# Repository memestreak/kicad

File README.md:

# KiCad

This repo contains my Kicad projects, custom libraries, and settings.

## Libraries

*   Footprints: `jme.pretty/`.
*   Symbols: `jme-symbols.kicad_sym`.

## Projects

Various projects, mostly related to audio and Eurorack.
                 
## Preferences

In the version-specific directories there are KiCad user preferences.

In order for KiCad to use them, you should replace the existing KiCad
user preference directory with a soft link to this directory.

E.g.,

```
# On Mac, for Kicad 7.0:

mv ~/Library/Preferences/kicad/7.0 ~/~/Library/Preferences/kicad/7.0_orig
ln -s ~/repos/kicad/7.0/preferences ~/Library/Preferences/kicad/7.0
```

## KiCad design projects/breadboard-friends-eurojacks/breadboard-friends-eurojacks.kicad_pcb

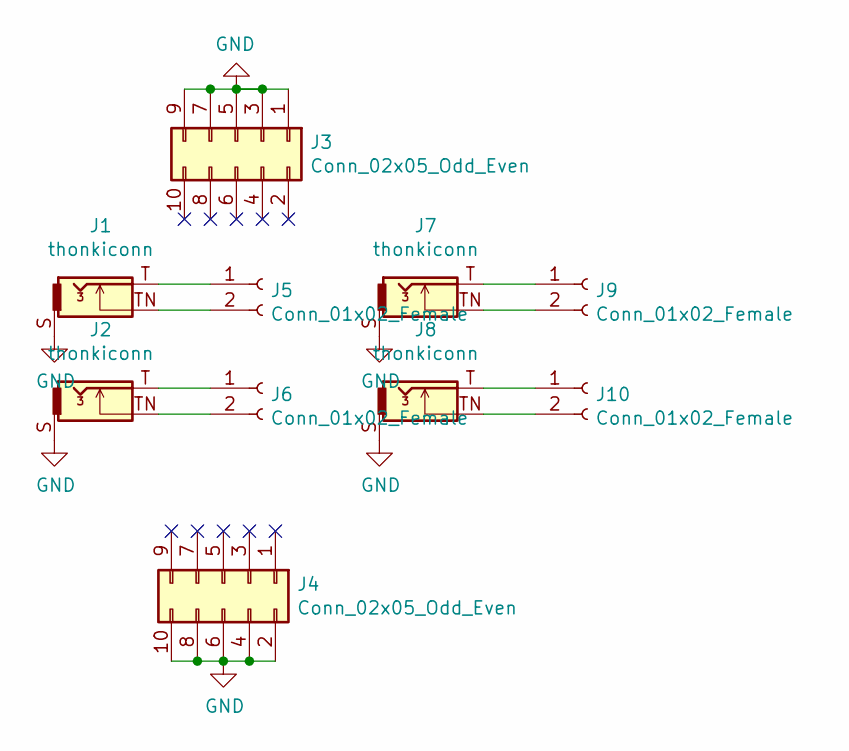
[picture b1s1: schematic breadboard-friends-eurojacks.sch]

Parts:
J1, J2, J7, J8: thonkiconn; Jack_3.5mm_QingPu_WQP-PJ398SM_Vertical_CircularHoles
J3, J4: Conn_02x05_Odd_Even; PinHeader_2x05_P2.54mm_Vertical
J5, J6, J9, J10: Conn_01x02_Female; PinSocket_1x02_P2.54mm_Vertical

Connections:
GND: J1.S, J2.S, J3.1, J3.3, J3.5, J3.7, J3.9, J4.2, J4.4, J4.6, J4.8, J4.10, J7.S, J8.S
unnamed: J1.T, J5.1
unnamed: J1.TN, J5.2
unnamed: J2.T, J6.1
unnamed: J2.TN, J6.2
unnamed: J7.T, J9.1
unnamed: J7.TN, J9.2
unnamed: J8.T, J10.1
unnamed: J8.TN, J10.2

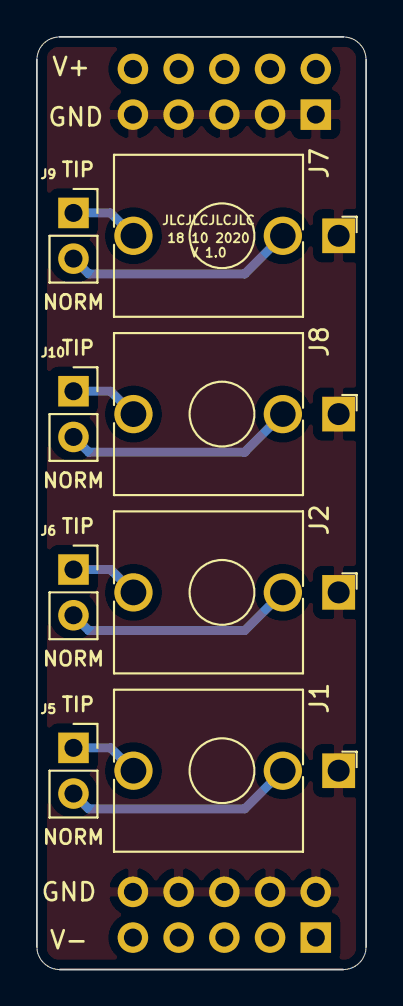
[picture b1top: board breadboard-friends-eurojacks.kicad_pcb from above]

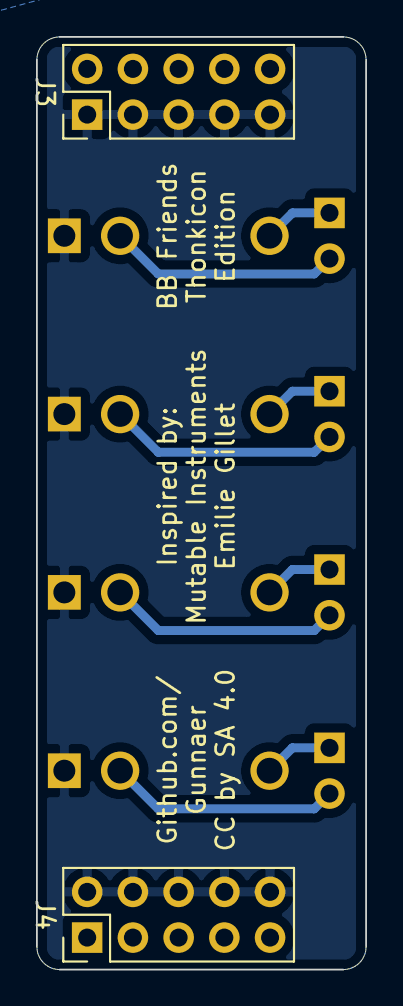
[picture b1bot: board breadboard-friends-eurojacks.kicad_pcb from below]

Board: 2 copper layers, 18.3 x 51.8 mm, 10 parts (2 on the bottom side), 9 nets.

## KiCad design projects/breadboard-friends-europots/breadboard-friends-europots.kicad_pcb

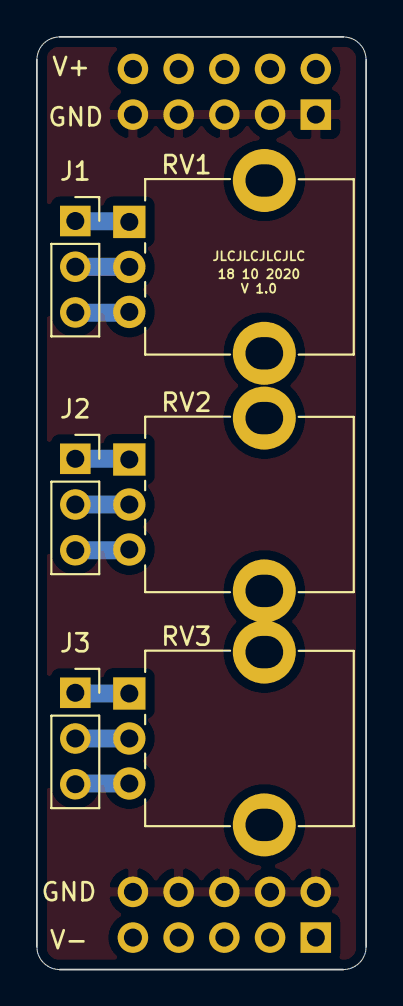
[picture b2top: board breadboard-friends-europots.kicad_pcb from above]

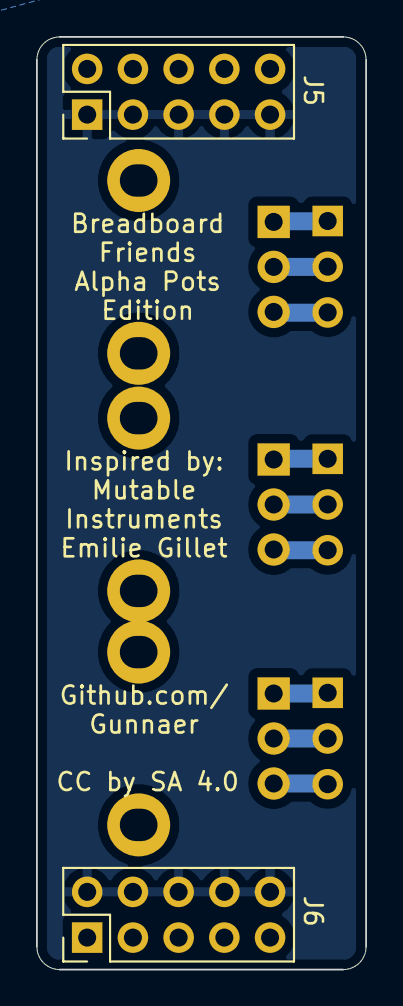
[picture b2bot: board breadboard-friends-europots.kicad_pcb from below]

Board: 2 copper layers, 18.3 x 51.8 mm, 8 parts (2 on the bottom side), 10 nets.

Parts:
J1, J2, J3: Conn_01x03_Female; PinSocket_1x03_P2.54mm_Vertical
J5, J6: Conn_02x05_Odd_Even; PinHeader_2x05_P2.54mm_Vertical
RV1, RV2, RV3: R_POT; Alpha_Potentiometer_2.1mmOval_Holes

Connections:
GND: J5.1, J5.3, J5.5, J5.7, J5.9, J6.2, J6.4, J6.6, J6.8, J6.10
unnamed: J1.1, RV1.1
unnamed: J1.2, RV1.2
unnamed: J1.3, RV1.3
unnamed: J2.1, RV2.1
unnamed: J2.2, RV2.2
unnamed: J2.3, RV2.3
unnamed: J3.1, RV3.1
unnamed: J3.2, RV3.2
unnamed: J3.3, RV3.3

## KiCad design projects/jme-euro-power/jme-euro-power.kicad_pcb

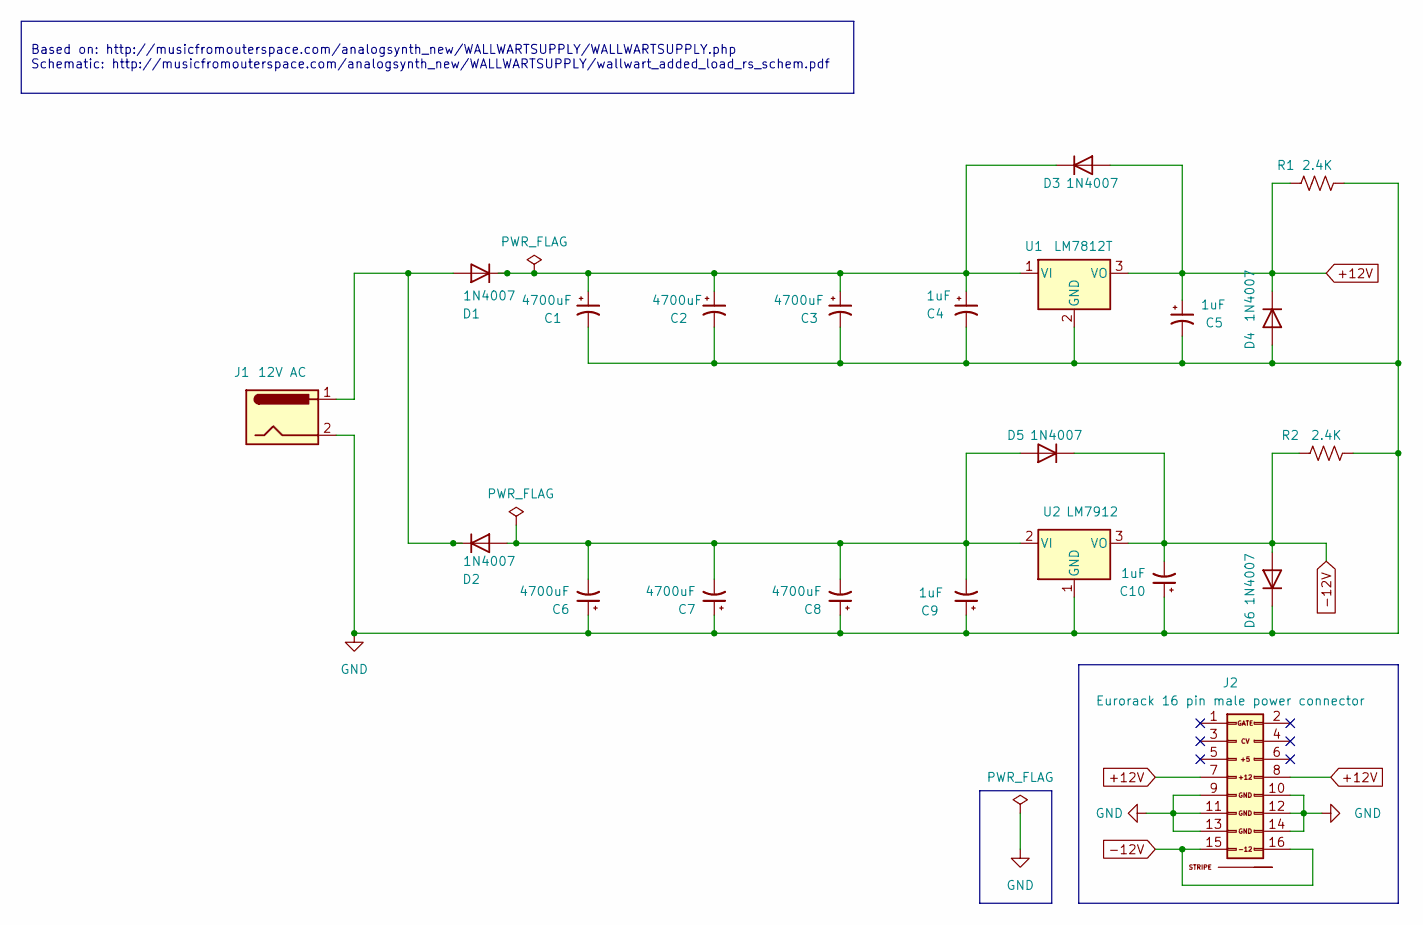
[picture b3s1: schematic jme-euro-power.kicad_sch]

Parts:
C1, C2, C3, C6, C7, C8: 4700uF; CP_Radial_D16.0mm_P7.50mm
C4, C5, C9, C10: 1uF; C_Disc_D7.5mm_W5.0mm_P5.00mm
D1: 1N4007; D_DO-35_P7.62mm_Horizontal
D2, D3, D4, D5, D6: 1N4007; D_DO-41_SOD81_P10.16mm_Horizontal
J1: 12V AC; BarrelJack_CUI_PJ-102AH_Horizontal
J2: Eurorack 16 pin male power connector; Pins_2x08_2.54mm_TH_EuroPower_Shrouded; Part Number LL1007-1 (2*8 HITEMP)
R1, R2: 2.4K; R_Box_L14.0mm_W5.0mm_P9.00mm
U1: LM7812T; TO-220-3_Vertical
U2: LM7912; TO-220-3_Vertical

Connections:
+12V: C5.1, D3.2 (A), D4.1 (K), J2.7 (12V), J2.8 (+12V), R1.1, U1.3 (VO)
-12V: C10.2, D5.1 (K), D6.2 (A), J2.15 (-12V), J2.16, R2.1, U2.3 (VO)
GND: C1.2, C2.2, C3.2, C4.2, C5.2, C6.1, C7.1, C8.1, C9.1, C10.1, D4.2 (A), D6.1 (K), J1.2, J2.9 (GND), J2.10 (GND), J2.11 (GND), J2.12 (GND), J2.13 (-12), J2.14 (-12V), R1.2, R2.2, U1.2 (GND), U2.1 (GND)
unnamed: D1.2 (A), D2.1 (K), J1.1
unnamed: C1.1, C2.1, C3.1, C4.1, D1.1 (K), D3.1 (K), U1.1 (VI)
unnamed: C6.2, C7.2, C8.2, C9.2, D2.2 (A), D5.2 (A), U2.2 (VI)

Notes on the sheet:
Based on: http://musicfromouterspace.com/analogsynth_new/WALLWARTSUPPLY/WALLWARTSUPPLY.php Schematic: http://musicfromouterspace.com/analogsynth_new/WALLWARTSUPPLY/wallwart_added_load_rs_schem.pdf

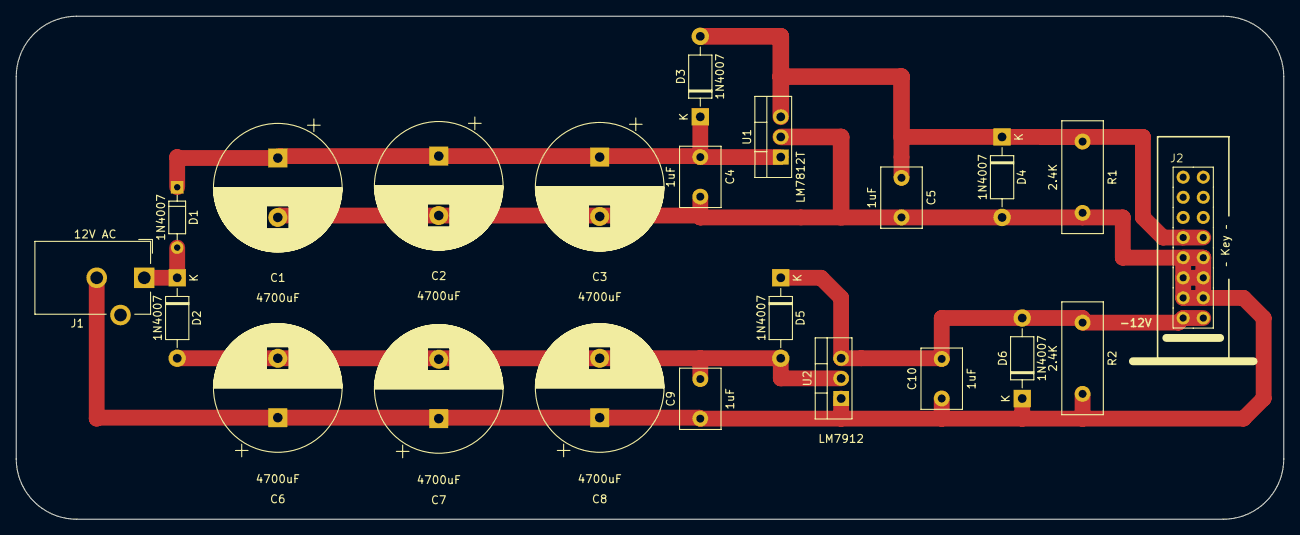
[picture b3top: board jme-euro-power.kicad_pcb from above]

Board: 2 copper layers, 160.0 x 63.5 mm, 22 parts (0 on the bottom side), 6 nets.

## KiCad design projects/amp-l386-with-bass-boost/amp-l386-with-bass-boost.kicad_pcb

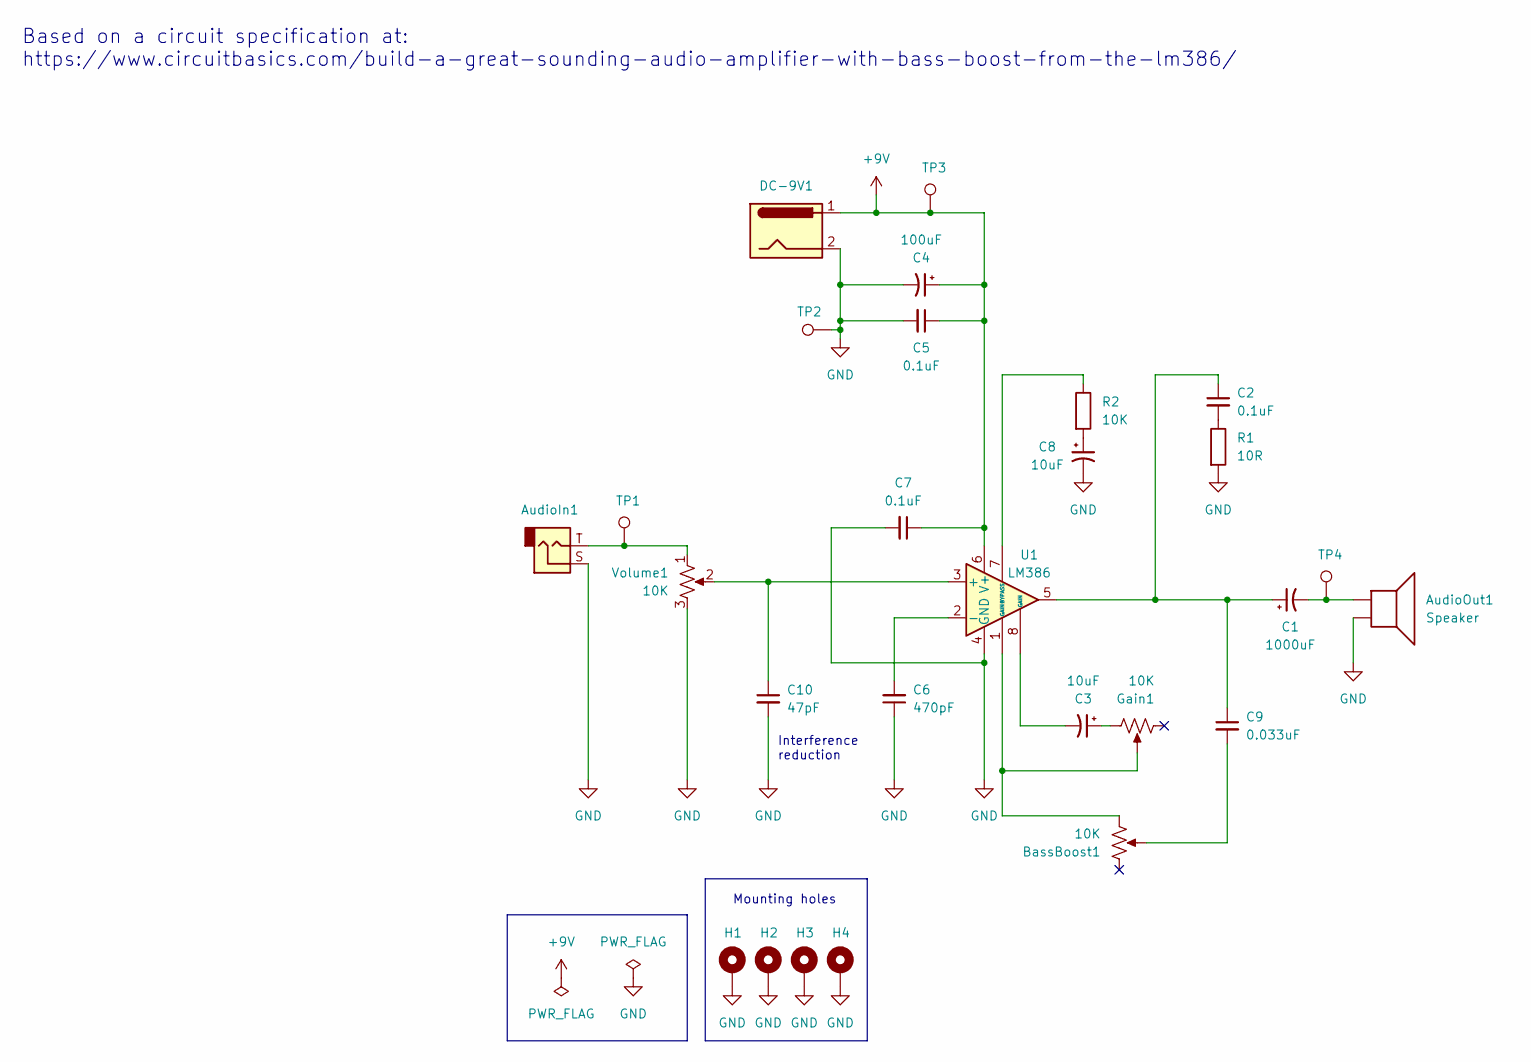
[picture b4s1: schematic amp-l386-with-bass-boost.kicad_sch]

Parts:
AudioIn1: AudioJack; jme-audio-pinheader-2.54-vertical
AudioOut1: Speaker; PinHeader_1x02_P2.54mm_Vertical
BassBoost1: 10K; PinHeader_1x03_P2.54mm_Vertical
C1: 1000uF; CP_Radial_D10.0mm_P5.00mm
C2, C7: 0.1uF; C_Disc_D5.1mm_W3.2mm_P5.00mm
C3, C8: 10uF; CP_Radial_D5.0mm_P2.50mm
C4: 100uF; CP_Radial_D6.3mm_P2.50mm
C5: 0.1uF; C_Rect_L7.0mm_W2.5mm_P5.00mm
C6: 470pF; C_Rect_L7.0mm_W2.5mm_P5.00mm
C9: 0.033uF; C_Disc_D5.1mm_W3.2mm_P5.00mm
C10: 47pF; C_Disc_D5.1mm_W3.2mm_P5.00mm
DC-9V1: Jack-DC; PinHeader_1x02_P2.54mm_Vertical
Gain1: 10K; PinHeader_1x03_P2.54mm_Vertical
H1, H2, H3, H4: MountingHole_Pad; MountingHole_3.2mm_M3_DIN965_Pad
R1: 10R; R_Axial_DIN0414_L11.9mm_D4.5mm_P20.32mm_Horizontal
R2: 10K; R_Axial_DIN0414_L11.9mm_D4.5mm_P20.32mm_Horizontal
TP1, TP2, TP3, TP4: TestPoint; TestPoint_Pad_2.0x2.0mm
U1: LM386; DIP-8_W7.62mm_Socket
Volume1: 10K; PinHeader_1x03_P2.54mm_Vertical

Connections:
+9V: C4.1, C5.1, C7.1, DC-9V1.1, TP3.1, U1.6 (V+)
GND: AudioIn1.S, AudioOut1.2, C4.2, C5.2, C6.1, C7.2, C8.2, C10.2, DC-9V1.2, H1.1, H2.1, H3.1, H4.1, R1.2, TP2.1, U1.4 (GND), Volume1.3
unnamed: AudioIn1.T, TP1.1, Volume1.1
unnamed: AudioOut1.1, C1.2, TP4.1
unnamed: BassBoost1.1, Gain1.2, U1.1 (GAIN)
unnamed: BassBoost1.2, C9.2
unnamed: C1.1, C2.1, C9.1, U1.5
unnamed: C2.2, R1.1
unnamed: C3.1, Gain1.3
unnamed: C3.2, U1.8 (GAIN)
unnamed: C6.2, U1.2 (-)
unnamed: C8.1, R2.2
unnamed: C10.1, U1.3 (+), Volume1.2
unnamed: R2.1, U1.7 (BYPASS)

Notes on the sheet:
Mounting holes
Based on a circuit specification at: https://www.circuitbasics.com/build-a-great-sounding-audio-amplifier-with-bass-boost-from-the-lm386/
Interference reduction

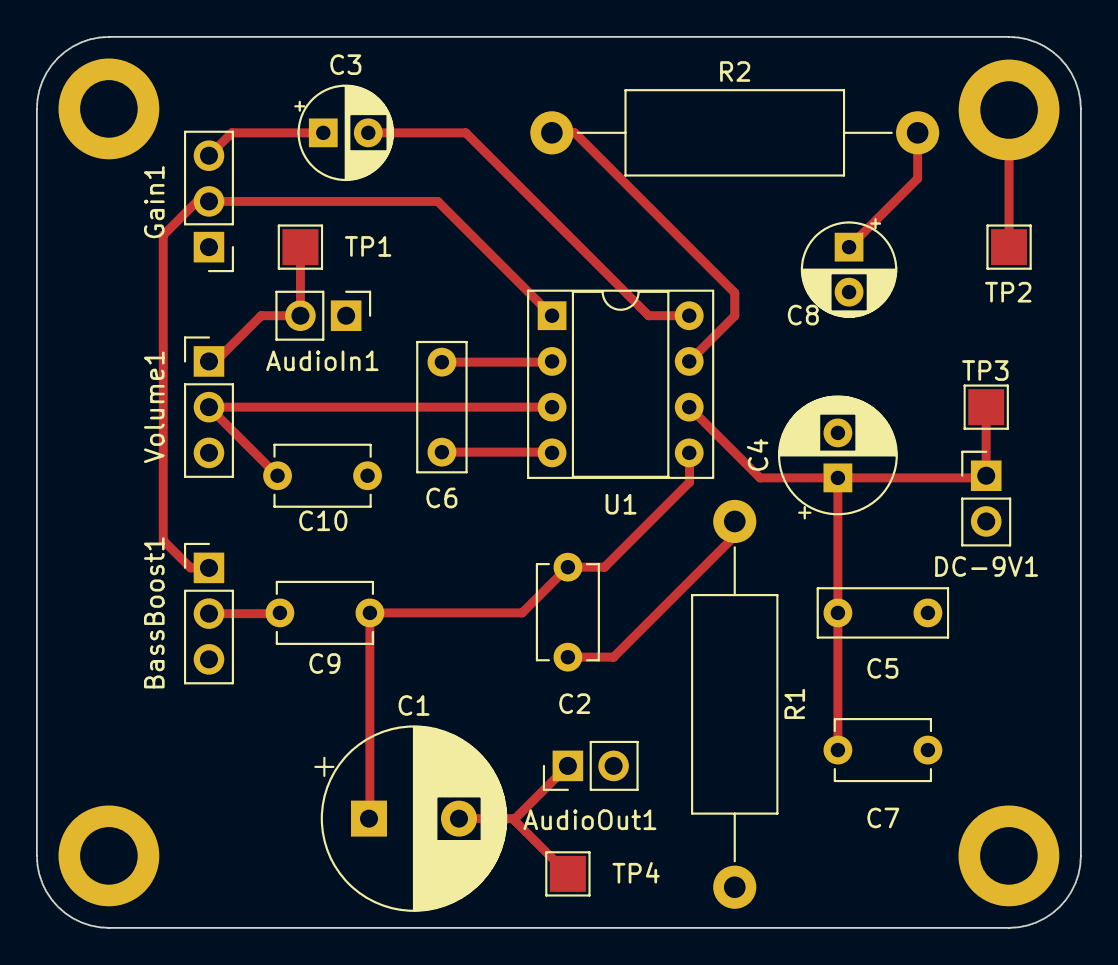
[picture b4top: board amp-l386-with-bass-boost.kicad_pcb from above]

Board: 2 copper layers, 58.0 x 49.5 mm, 27 parts (0 on the bottom side), 14 nets.

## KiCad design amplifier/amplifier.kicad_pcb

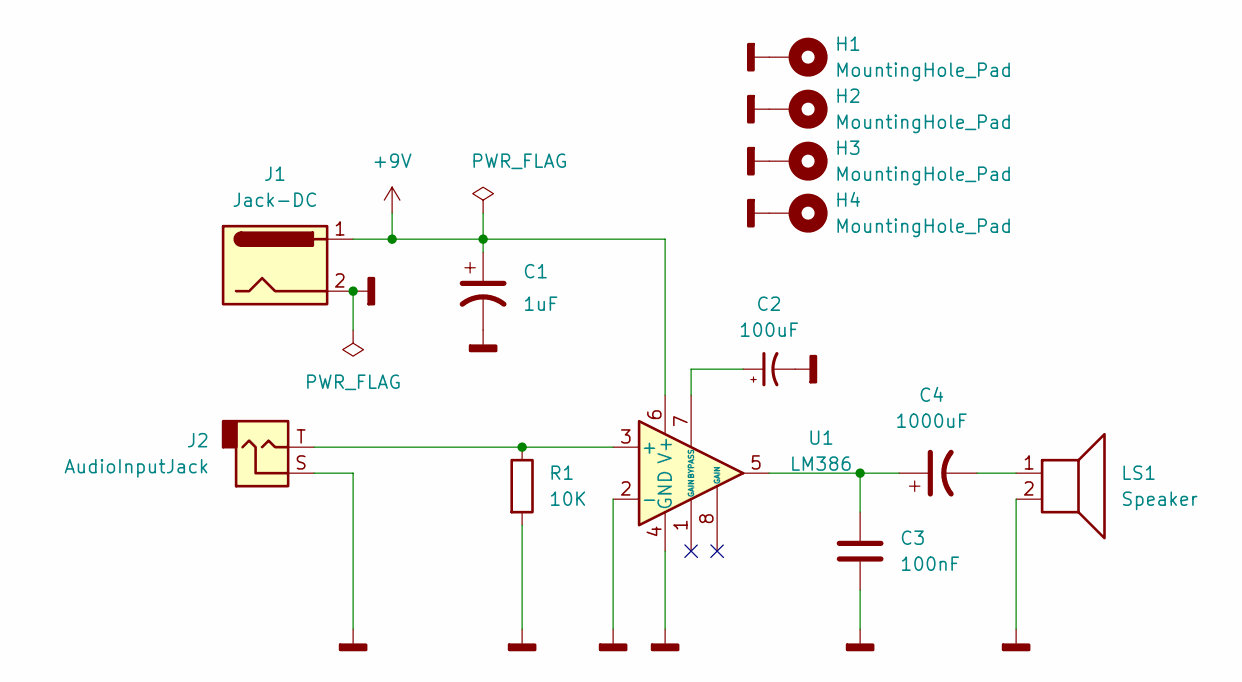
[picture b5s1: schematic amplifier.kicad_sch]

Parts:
C1: 1uF; CP_Radial_D5.0mm_P2.50mm
C2: 100uF; CP_Radial_D5.0mm_P2.50mm
C3: 100nF; C_Disc_D3.0mm_W1.6mm_P2.50mm
C4: 1000uF; CP_Radial_D10.0mm_P7.50mm
H1, H2, H3, H4: MountingHole_Pad; MountingHole_3.2mm_M3_Pad
J1: Jack-DC; PinHeader_1x02_P2.54mm_Vertical
J2: AudioInputJack; AudioJack_Mono_PinHeader_1x02_P2.54mm_Vertical
LS1: Speaker; PinHeader_1x02_P2.54mm_Vertical
R1: 10K; R_Axial_DIN0309_L9.0mm_D3.2mm_P12.70mm_Horizontal
U1: LM386; DIP08

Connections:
+9V: C1.1, J1.1, U1.6 (V+)
GNDD: C1.2, C2.2, C3.2, H1.1, H2.1, H3.1, H4.1, J1.2, J2.S, LS1.2, R1.2, U1.2 (-), U1.4 (GND)
unnamed: C2.1, U1.7 (BYPASS)
unnamed: C3.1, C4.1, U1.5
unnamed: C4.2, LS1.1
unnamed: J2.T, R1.1, U1.3 (+)

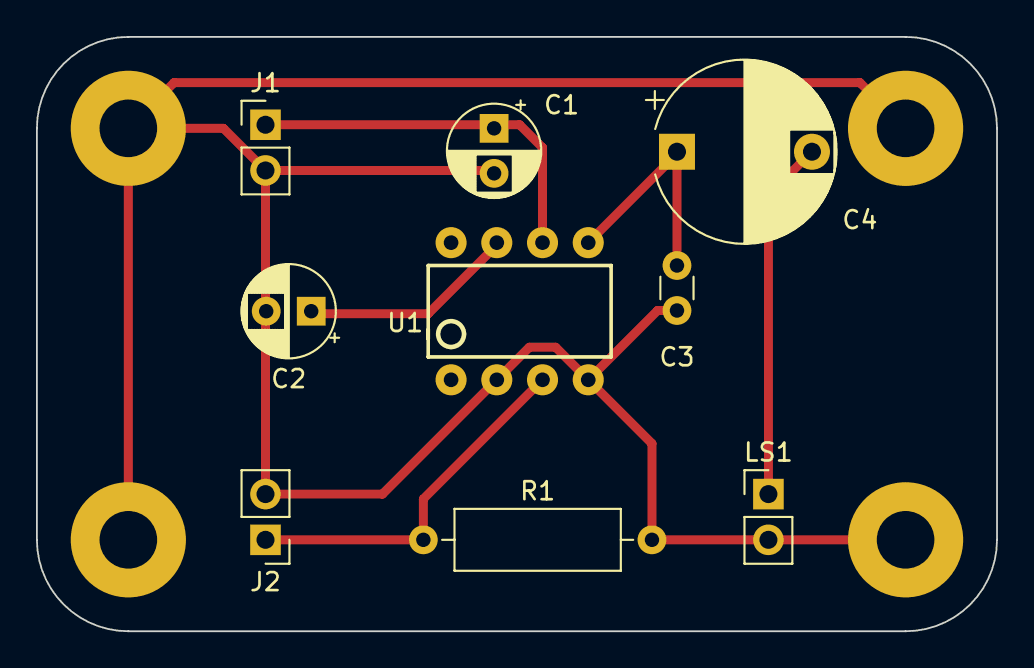
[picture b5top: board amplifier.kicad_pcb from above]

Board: 2 copper layers, 53.3 x 33.0 mm, 13 parts (0 on the bottom side), 6 nets.

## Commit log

2023-01-15 Initial commit of personal kicad project tree
2023-01-16 Adding link to source for simple amp project
2023-01-16 Adding .gitingore file for kicad temp file etc.
2023-01-16 Checkpoint of lm386 amp with schematic and annotations
2023-01-17 Change audio pin header footprint to T and S for tip and sleeve
2023-01-17 Initial checkin of l386 amp with bass boost
2023-01-17 Initial checkin of amp-l386-with-bass-boost project
2023-01-18 Checking initial PCB placement of bassboost project
2023-01-21 Progress on amp-l386-with-bass-boost layout. Still need real footprints
2023-01-21 Add copper ground plane to PCB
2023-01-21 Incremental changes optimizing PCB layout
2023-01-22 Cleaned up with cut layer. Possibly complete. Time to validate.
2023-01-23 Correct several capacitor footprints (should be axial).
2023-01-26 Add test points
2023-02-06 Remove old directory pre-projects directory creation.
2023-07-05 Initial checkin of Eurorack power schematic. PCB incomplete.
    This is based on work from Music From Outer Space:
    http://musicfromouterspace.com/analogsynth_new/WALLWARTSUPPLY/WALLWARTSUPPLY.php
    http://musicfromouterspace.com/analogsynth_new/WALLWARTSUPPLY/wallwart_added_load_rs_schem.pdf
2023-07-05 Incremental checkin of schematic
2023-07-05 Completed PCB optimized for stripboard. All warnings resolved.
2023-07-05 Make layout smaller to accomodate strip board available.
2023-08-04 incrmental update to power supply schematic
2024-01-18 Initial checkin of kicad 7.0 user preferences
2024-01-18 Preferences update
2024-01-18 Initial checkin of copied breadboard jacks and pots projects.
    This content originates from github.com/gunnaer/PCB-Friends.
2024-03-18 Move README.org to the top level.
2024-03-18 Fix typos in REAME. Move symbol library to new symbols/ directory.

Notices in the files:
projects/breadboard-friends-eurojacks/breadboard-friends-eurojacks.kicad_pcb:
CC by SA 4.0
